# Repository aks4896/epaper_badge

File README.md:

# epaper_badge
Project to create conference badge using epaper display

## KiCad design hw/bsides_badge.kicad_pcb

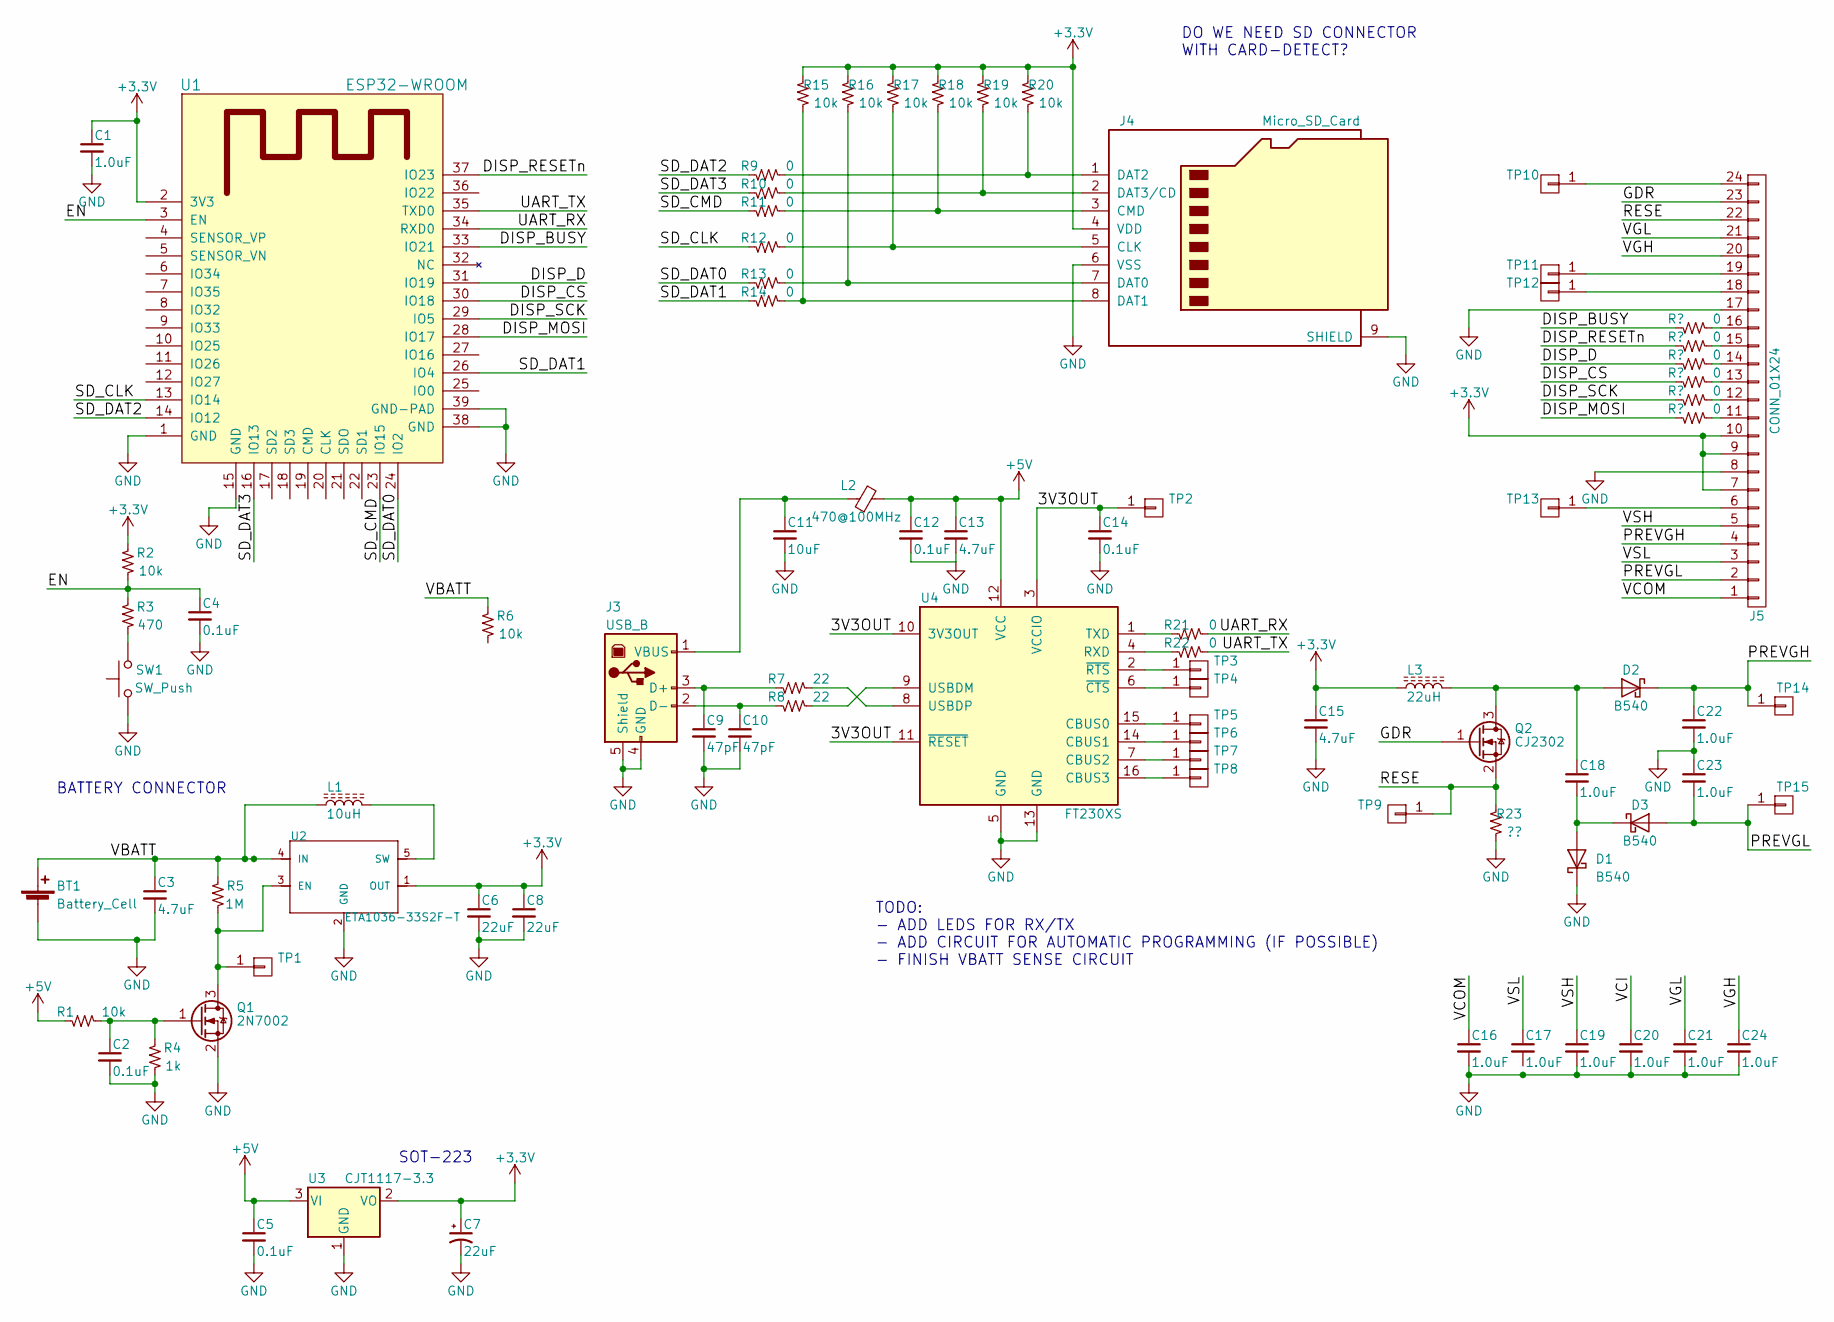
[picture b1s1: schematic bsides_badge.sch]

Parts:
BT1: Battery_Cell; Keystone_2466_1xAAA
C1, C16, C17, C18, C19, C20, C21, C22, C23, C24: 1.0uF; C_0603
C2, C4, C5, C12, C14: 0.1uF; C_0603
C3, C13, C15: 4.7uF; C_0603
C6, C8: 22uF; C_0805
C7: 22uF; CP_Tantalum_Case-A_EIA-3216-18_Reflow
C9, C10: 47pF; C_0603
C11: 10uF; C_0603
D1, D2, D3: B540; D_SOD-123
J3: USB_B; USB_Micro-B_Molex_47346-0001
J4: Micro_SD_Card; MICRO-SD9+4P-SMD-16.1X14.5X1.85MM
J5: CONN_01X24; Hirose_FH12-24S-0.5SH_1x24_P0.5mm_Horizontal
L1: 10uH; L_Taiyo-Yuden_NR-60xx_HandSoldering
L2: 470@100MHz; L_0805
L3: 22uH; L_Taiyo-Yuden_NR-40xx_HandSoldering
Q1: 2N7002; SOT-23
Q2: CJ2302; SOT-23
R1, R2, R6, R15, R16, R17, R18, R19, R20: 10k; R_0603
R3: 470; R_0603
R4: 1k; R_0603
R5: 1M; R_0603
R7, R8: 22; R_0603
R9, R10, R11, R12, R13, R14, R21, R22: 0; R_0603
R23: ??; R_0603
SW1: SW_Push; SW_SPST_SKQG
TP1, TP2, TP3, TP4, TP5, TP6, TP7, TP8, TP9, TP10, TP11, TP12, TP13, TP14, TP15: TEST_POINT; SolderWirePad_single_0-8mmDrill; MPN DO_NOT_POPULATE
U1: ESP32-WROOM; MPN ESP32-WROOM-32
U2: ETA1036-33S2F-T; SOT-23-5; MPN ETA1036-33S2F-T
U3: CJT1117-3.3; SOT-223-3_TabPin2
U4: FT230XS; SSOP-16_3.9x4.9mm_Pitch0.635mm

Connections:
+3V3: C1.1, C6.1, C7.1, C8.1, C15.1, J4.4 (VDD), J5.7, J5.9, J5.10, L3.1, R2.2, R15.2, R16.2, R17.2, R18.2, R19.2, R20.2, U1.2 (3V3), U2.1 (OUT), U3.2 (VO)
+5V: C5.1, C12.1, C13.1, L2.2, R1.2, U3.3 (VI), U4.12 (VCC)
/3V3OUT: C14.1, TP2.1, U4.3 (VCCIO), U4.10 (3V3OUT), U4.11 (~RESET)
/DISP_BUSY: J5.16, U1.33 (IO21)
/DISP_CS: J5.13, U1.30 (IO18)
/DISP_D: J5.14, U1.31 (IO19)
/DISP_MOSI: J5.11, U1.28 (IO17)
/DISP_RESETn: J5.15, U1.37 (IO23)
/DISP_SCK: J5.12, U1.29 (IO5)
/EN: C4.1, R2.1, R3.2, U1.3 (EN)
/GDR: J5.23, Q2.1 (G)
/PREVGH: C22.1, D2.1 (K), J5.4, TP14.1
/PREVGL: C23.2, D3.2 (A), J5.2, TP15.1
/RESE: J5.22, Q2.2 (S), R23.2, TP9.1
/SD_CLK: R12.2, U1.13 (IO14)
/SD_CMD: R11.2, U1.23 (IO15)
/SD_DAT0: R13.2, U1.24 (IO2)
/SD_DAT1: R14.2, U1.26 (IO4)
/SD_DAT2: R9.2, U1.14 (IO12)
/SD_DAT3: R10.2, U1.16 (IO13)
/UART_RX: R21.1, U1.34 (RXD0)
/UART_TX: R22.1, U1.35 (TXD0)
/VBATT: BT1.1 (+), C3.1, L1.1, R5.2, R6.2, U2.4 (IN)
/VCI: C20.1
/VCOM: C16.1, J5.1
/VGH: C24.1, J5.20
/VGL: C21.1, J5.21
/VSH: C19.1, J5.5
/VSL: C17.1, J5.3
GND: BT1.2 (-), C1.2, C2.2, C3.2, C4.2, C5.2, C6.2, C7.2, C8.2, C9.2, C10.2, C11.2, C12.2, C13.2, C14.2, C15.2, C16.2, C19.2, C20.2, C21.2, C22.2, C23.1, C24.2, D1.1 (K), J3.4 (GND), J3.5 (Shield), J4.6 (VSS), J4.9 (SHIELD), J5.8, J5.17, Q1.2 (S), R4.1, R23.1, SW1.1, U1.1 (GND), U1.15 (GND), U1.38 (GND), U1.39 (GND-PAD), U2.2 (GND), U3.1 (GND), U4.5 (GND), U4.13 (GND)
unnamed: C2.1, Q1.1 (G), R1.1, R4.2
unnamed: C9.1, J3.3 (D+), R7.2
unnamed: C10.1, J3.2 (D-), R8.2
unnamed: C11.1, J3.1 (VBUS), L2.1
unnamed: C18.1, D2.2 (A), L3.2, Q2.3 (D)
unnamed: C18.2, D1.2 (A), D3.1 (K)
unnamed: J4.1 (DAT2), R9.1, R20.1
unnamed: J4.2 (DAT3/CD), R10.1, R19.1
unnamed: J4.3 (CMD), R11.1, R18.1
unnamed: J4.5 (CLK), R12.1, R17.1
unnamed: J4.7 (DAT0), R13.1, R16.1
unnamed: J4.8 (DAT1), R14.1, R15.1
unnamed: J5.6, TP13.1
unnamed: J5.18, TP12.1
unnamed: J5.19, TP11.1
unnamed: J5.24, TP10.1
unnamed: L1.2, U2.5 (SW)
unnamed: Q1.3 (D), R5.1, TP1.1, U2.3 (EN)
unnamed: R3.1, SW1.2
unnamed: R7.1, U4.8 (USBDP)
unnamed: R8.1, U4.9 (USBDM)
unnamed: R21.2, U4.1 (TXD)
unnamed: R22.2, U4.4 (RXD)
unnamed: TP3.1, U4.2 (~RTS)
unnamed: TP4.1, U4.6 (~CTS)
unnamed: TP5.1, U4.15 (CBUS0)
unnamed: TP6.1, U4.14 (CBUS1)
unnamed: TP7.1, U4.7 (CBUS2)
unnamed: TP8.1, U4.16 (CBUS3)

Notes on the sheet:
BATTERY CONNECTOR
SOT-223
DO WE NEED SD CONNECTOR WITH CARD-DETECT?
TODO: - ADD LEDS FOR RX/TX - ADD CIRCUIT FOR AUTOMATIC PROGRAMMING (IF POSSIBLE) - FINISH VBATT SENSE CIRCUIT

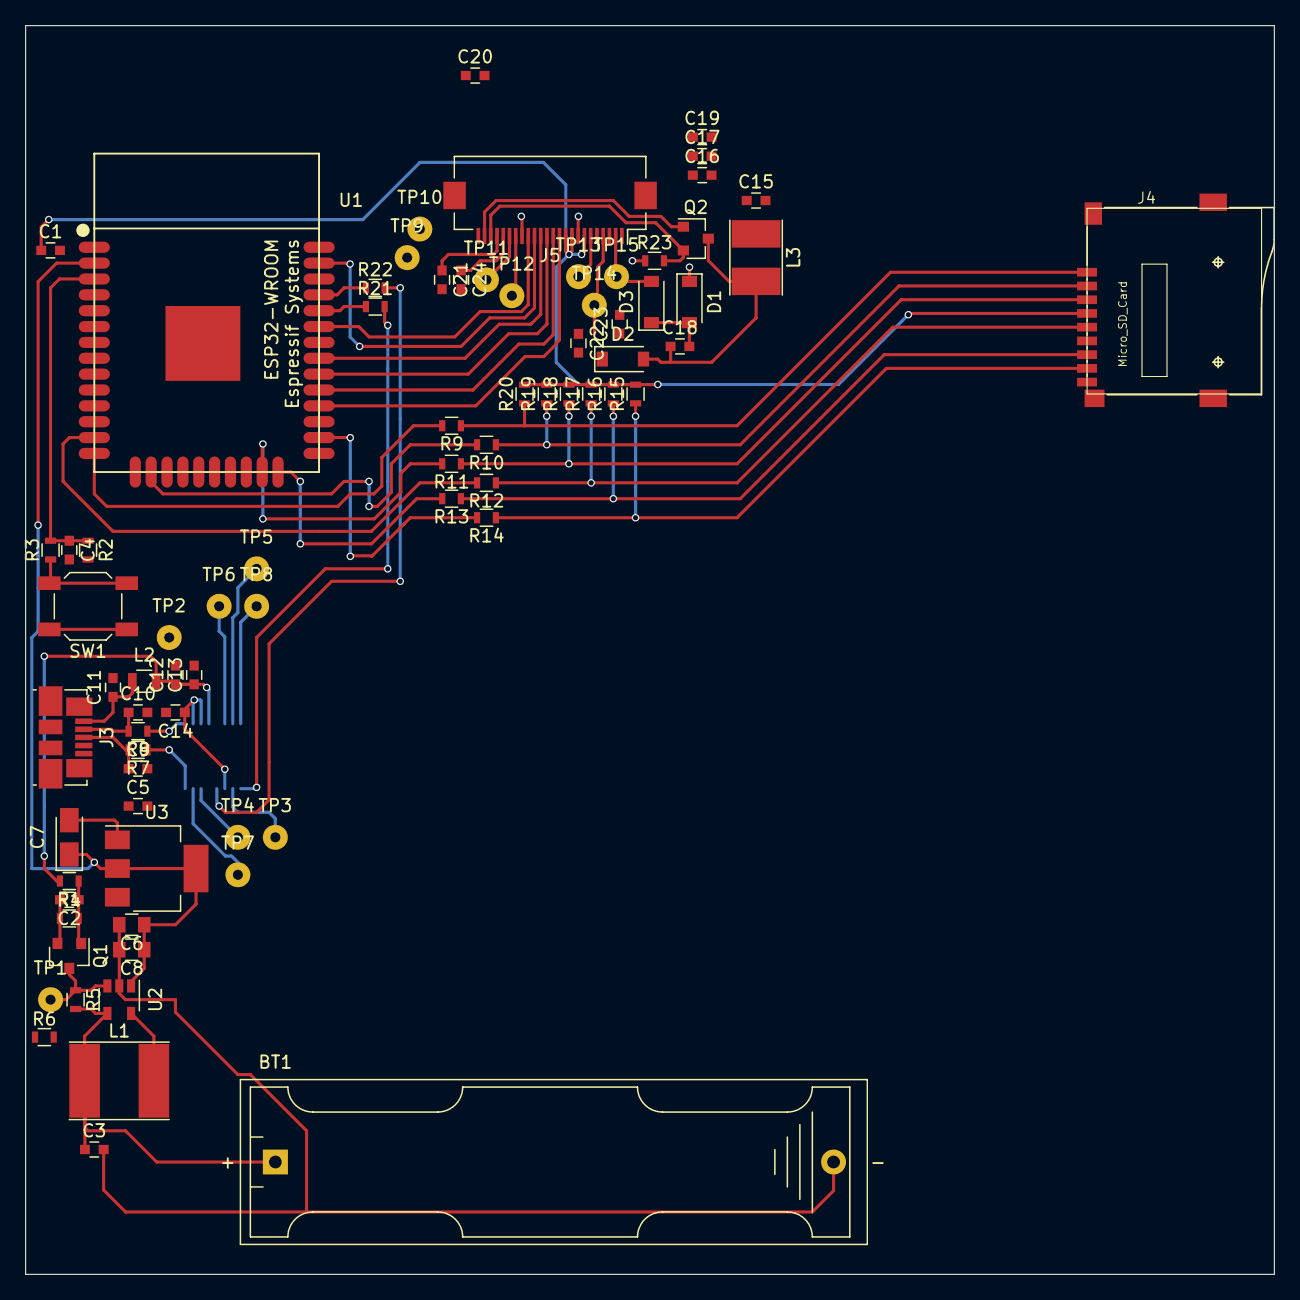
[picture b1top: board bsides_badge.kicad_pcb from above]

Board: 2 copper layers, 100.0 x 100.0 mm, 79 parts (1 on the bottom side), 58 nets.

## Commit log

2017-08-12 Hardware: Initial design, still lots more to do
    - Most parts placed
    - Created datasheet directory
    - Created gitignore to skip *.bak files
2017-08-12 Hardware: Added markdown with links to libraries used.
    I could/should add these as submodules someday...
2017-08-12 Hardware: More progress, got FTDI chip wired up
2017-08-15 Hardware: Finished power supplies, SD Card, started display
2017-08-15 Hardware: Added additional datasheets
    - Mosfet Datasheet (for boost in display interface)
    - Diode Datasheet (for boost in display interface)
    - Inductor Datasheet (expected to be used in battery boost)
2017-08-16 Hardware: Connected LCD in schematic
2017-12-02 hw: cleaned up part numbers, exported initial BOM
2017-12-02 hw: consolidated the schematics to 1 page
2017-12-02 hw: netlisted and placed components
2017-12-02 hw: Board partially routed
    - Board initially routed
    - Started on BOM for system
    - Added 0-ohm resistors to SPI lines in e-paper display
    -- Need to netlist this still
    - Added TODO list in schematic
2018-04-14 hw: Completed most of the routing
